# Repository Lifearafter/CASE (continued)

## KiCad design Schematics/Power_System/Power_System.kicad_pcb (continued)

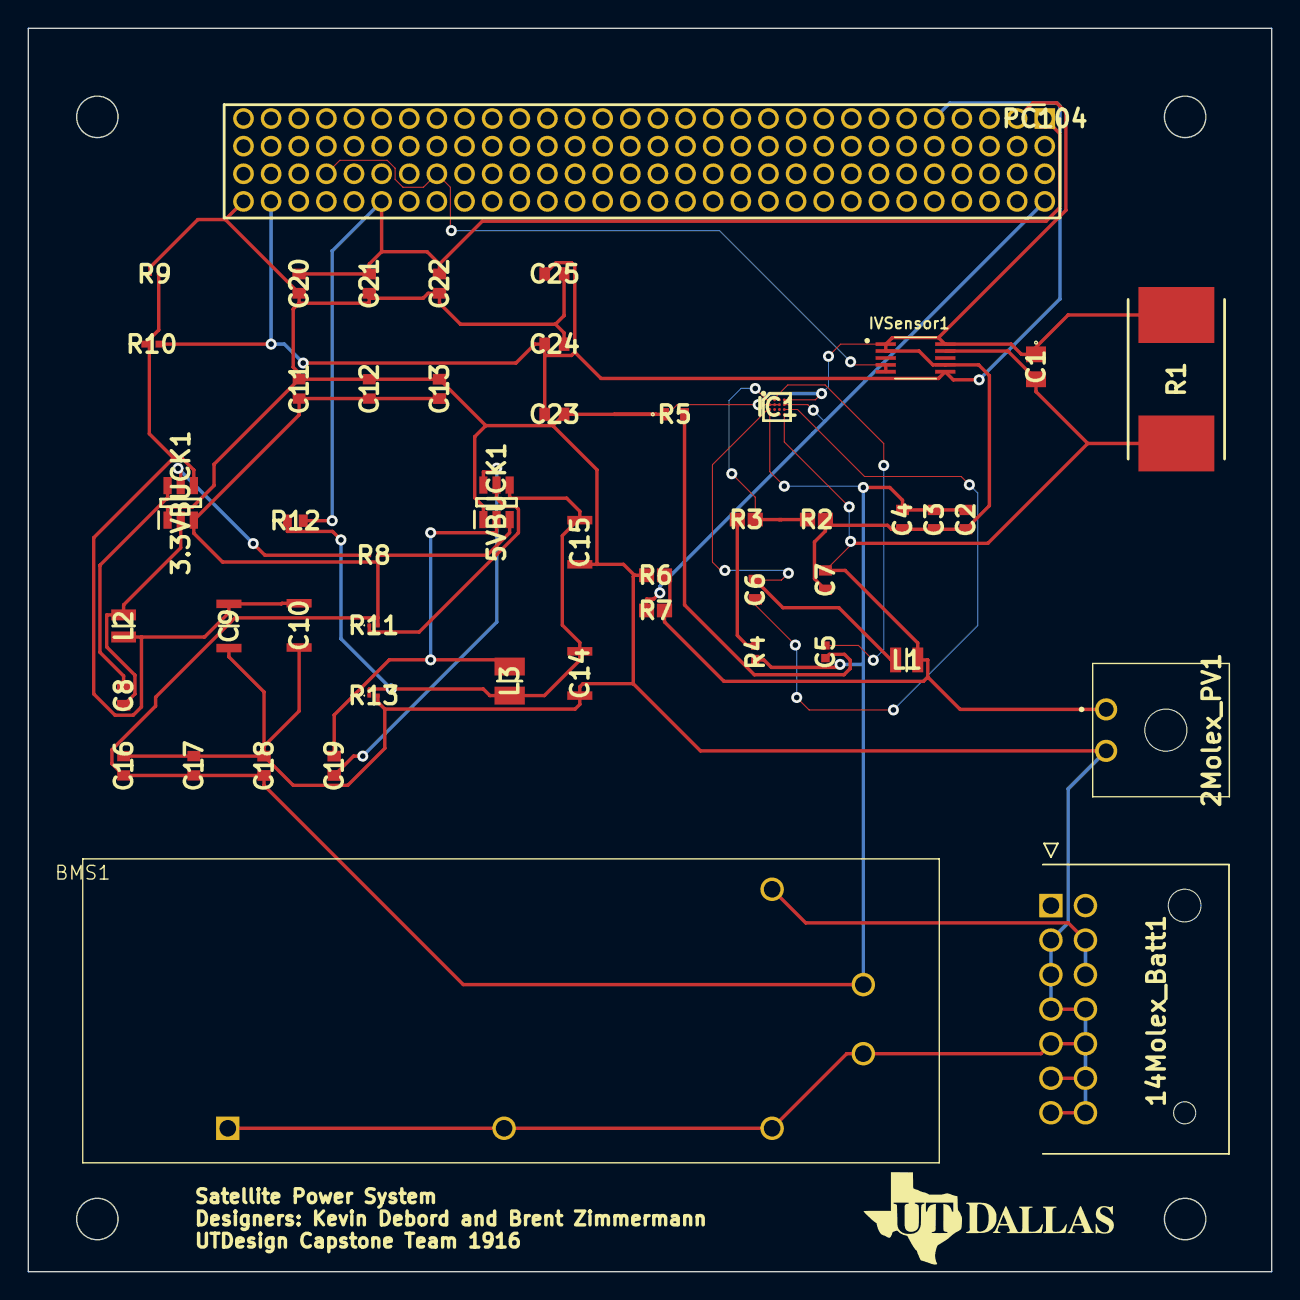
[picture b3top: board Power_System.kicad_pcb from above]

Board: 2 copper layers, 90.0 x 90.0 mm, 49 parts (0 on the bottom side), 23 nets.

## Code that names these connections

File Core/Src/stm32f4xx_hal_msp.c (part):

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
    __HAL_RCC_GPIOB_CLK_ENABLE();
    /**I2C1 GPIO Configuration
    PB6     ------> I2C1_SCL
    PB7     ------> I2C1_SDA
    */
    GPIO_InitStruct.Pin = GPIO_PIN_6|GPIO_PIN_7;
    GPIO_InitStruct.Mode = GPIO_MODE_AF_OD;
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    __HAL_RCC_I2C1_CLK_DISABLE();

    /**I2C1 GPIO Configuration
    PB6     ------> I2C1_SCL
    PB7     ------> I2C1_SDA
    */
    HAL_GPIO_DeInit(GPIOB, GPIO_PIN_6);

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
    __HAL_RCC_GPIOA_CLK_ENABLE();
    /**TIM2 GPIO Configuration
    PA0-WKUP     ------> TIM2_CH1
    */
    GPIO_InitStruct.Pin = GPIO_PIN_0;
    GPIO_InitStruct.Mode = GPIO_MODE_AF_PP;
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
    __HAL_RCC_GPIOA_CLK_ENABLE();
    /**USART2 GPIO Configuration
    PA2     ------> USART2_TX
    PA3     ------> USART2_RX
    */
    GPIO_InitStruct.Pin = USART_TX_Pin|USART_RX_Pin;
    GPIO_InitStruct.Mode = GPIO_MODE_AF_PP;
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    __HAL_RCC_USART2_CLK_DISABLE();

    /**USART2 GPIO Configuration
    PA2     ------> USART2_TX
    PA3     ------> USART2_RX
    */
    HAL_GPIO_DeInit(GPIOA, USART_TX_Pin|USART_RX_Pin);

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
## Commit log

2023-11-10 fix: readme formatting problems on github
2023-11-10 docs: add contributing text
2024-01-19 feat: restructuring of project, and addition of freeRtos
2024-01-19 feat: add task folder
2024-01-19 feat: add working blink example with freeRtos tasks
2024-01-19 feat: changes to the project structure, and makefile
2024-01-19 feat: add vscode configs for reference configuration of project
2024-01-19 feat: add gpio_mappings for the repo
2024-01-19 feat: NeoM8n SPI driver
2024-01-19 feat: add the driver templates for INA226, and LM75A using I2C interfaces
2024-01-26 feat: updates NeoM8n drivers for uart, and INA226 drivers with new registers and config
2024-01-27 feat: add LM75A Task to telemetry
2024-01-27 feat: working LM75A task
2024-01-28 feat: add COM support over USART for printf to console
2024-02-08 feat: working LM75A driver over I2C with fixed address 0x48
2024-02-08 feat: add com support to print explicit char arrays
2024-02-12 feat: INA260 driver update
2024-02-15 dependency: add NMEA parser for NEOM8N
2024-02-15 feat: add NMEA parsing to NeoM8N drivers
2024-02-15 feat: add parsing and buffer capabilities to NEOM8N driver
2024-02-15 feat: add ADXL345 driver capabilities
2024-02-16 feat: add ADXL345 funcs to make integration easier
2024-02-16 feat: circle buffer functionality to GPS
2024-02-16 feat: create files for new sensors
2024-03-05 feat: INA226 working code
2024-03-06 feat: working INA226 code, unit tested using a module
2024-03-26 feat: new drivers for LIS3MDL and IAM20380
2024-03-26 feat: add all kicad schematics for the project, seperated by subsystem ie Flight, Power, Comms
2024-03-28 feat: New and updated FC
2024-03-28 feat: cleaned up schematic for FC
2024-03-28 upto date req
2024-03-28 feat: new updated sch for better readibility
2024-03-28 updated pcb without traces or via's
2024-04-03 feat: add CC1120 drivers
2024-04-05 feat: add CC1120 FreeRTOS read task
2024-04-12 fix: add cc1120 bug fixes
